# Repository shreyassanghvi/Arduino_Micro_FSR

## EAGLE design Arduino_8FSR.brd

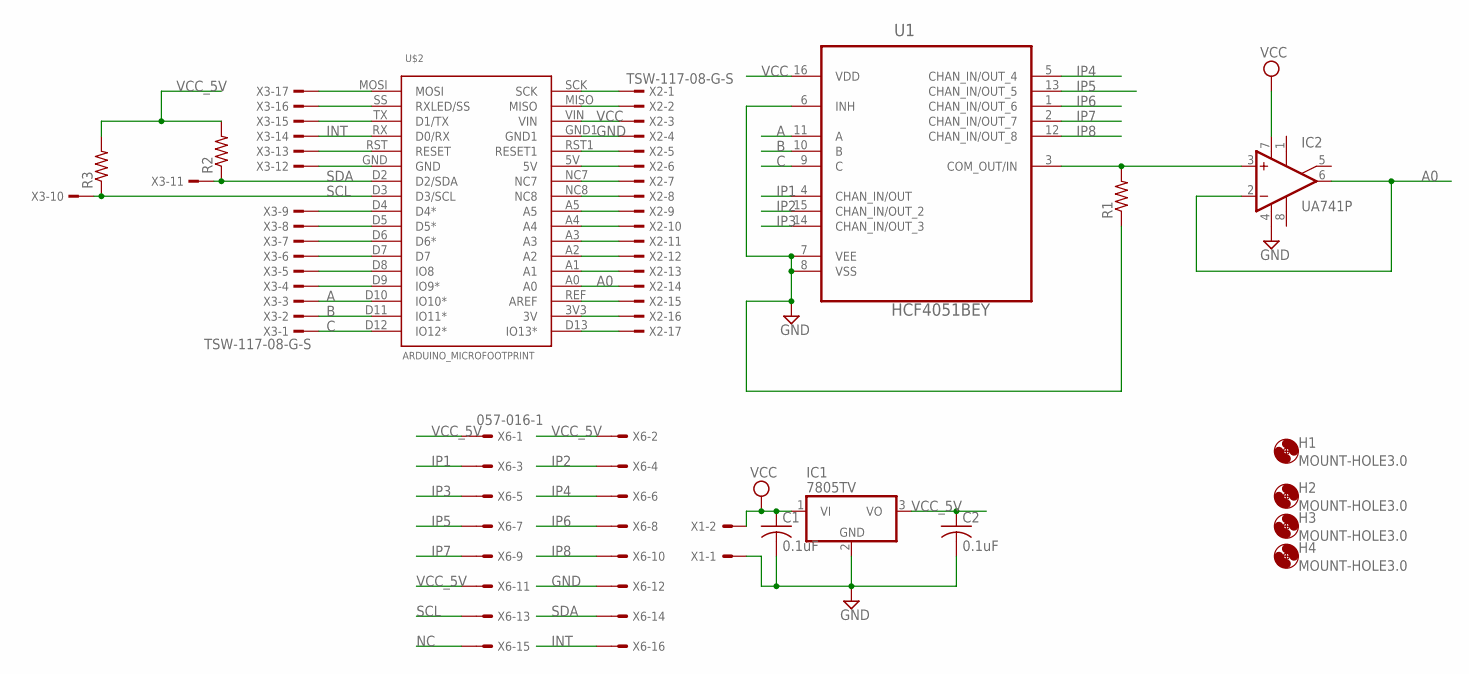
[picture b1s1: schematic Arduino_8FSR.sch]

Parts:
C1, C2: 0.1uF; C025-024X044
H1, H2, H3, H4: MOUNT-HOLE3.0; 3,0
IC1: 7805TV; TO220V
IC2: UA741P; DIL08
R1, R2, R3: R-US_0204/7; 0204/7
U1: HCF4051BEY; DIP254P762X510-16
U$2: ARDUINO_MICROFOOTPRINT; ARDUINO-MICRO
X1: KK-156-2
X2, X3: TSW-117-08-G-S; TSW-117-XX-G-S
X6: 057-016-1

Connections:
A: U1.11 (A), U$2.D10 (IO10*), X3.3
A0: IC2.2 (-IN), IC2.6 (OUT), U$2.A0, X2.14
B: U1.10 (B), U$2.D11 (IO11*), X3.2
C: U1.9 (C), U$2.D12 (IO12*), X3.1
GND: C1.2, C2.2, IC1.2 (GND), IC2.4 (V-), R1.1, U1.6 (INH), U1.7 (VEE), U1.8 (VSS), U$2.GND1, X1.1, X2.4, X6.12
INT: U$2.RX (D0/RX), X3.14, X6.16
IP1: U1.4 (CHAN_IN/OUT), X6.3
IP2: U1.15 (CHAN_IN/OUT_2), X6.4
IP3: U1.14 (CHAN_IN/OUT_3), X6.5
IP4: U1.5 (CHAN_IN/OUT_4), X6.6
IP5: U1.13 (CHAN_IN/OUT_5), X6.7
IP6: U1.1 (CHAN_IN/OUT_6), X6.8
IP7: U1.2 (CHAN_IN/OUT_7), X6.9
IP8: U1.12 (CHAN_IN/OUT_8), X6.10
unnamed: U$2.MOSI, X3.17
unnamed: U$2.SS (RXLED/SS), X3.16
unnamed: U$2.D13 (IO13*), X2.17
unnamed: U$2.D5 (D5*), X3.8
unnamed: U$2.RST (RESET), X3.13
unnamed: U$2.GND, X3.12
unnamed: U$2.D6 (D6*), X3.7
unnamed: U$2.D7, X3.6
unnamed: U$2.D4 (D4*), X3.9
unnamed: U$2.TX (D1/TX), X3.15
unnamed: U$2.D8 (IO8), X3.5
unnamed: U$2.D9 (IO9*), X3.4
unnamed: U$2.3V3 (3V), X2.16
unnamed: U$2.REF (AREF), X2.15
unnamed: U$2.A1, X2.13
unnamed: U$2.A2, X2.12
unnamed: U$2.A3, X2.11
unnamed: U$2.A4, X2.10
unnamed: U$2.A5, X2.9
unnamed: U$2.NC8, X2.8
unnamed: U$2.NC7, X2.7
unnamed: U$2.5V, X2.6
unnamed: U$2.RST1 (RESET1), X2.5
unnamed: U$2.MISO, X2.2
unnamed: U$2.SCK, X2.1
unnamed: IC2.3 (+IN), R1.2, U1.3 (COM_OUT/IN)
NC: X6.15
SCL: R3.1, U$2.D3 (D3/SCL), X3.10, X6.13
SDA: R2.1, U$2.D2 (D2/SDA), X3.11, X6.14
VCC: C1.1, IC1.1 (VI), IC2.7 (V+), U1.16 (VDD), U$2.VIN, X1.2, X2.3
VCC_5V: C2.1, IC1.3 (VO), R2.2, R3.2, X6.1, X6.2, X6.11

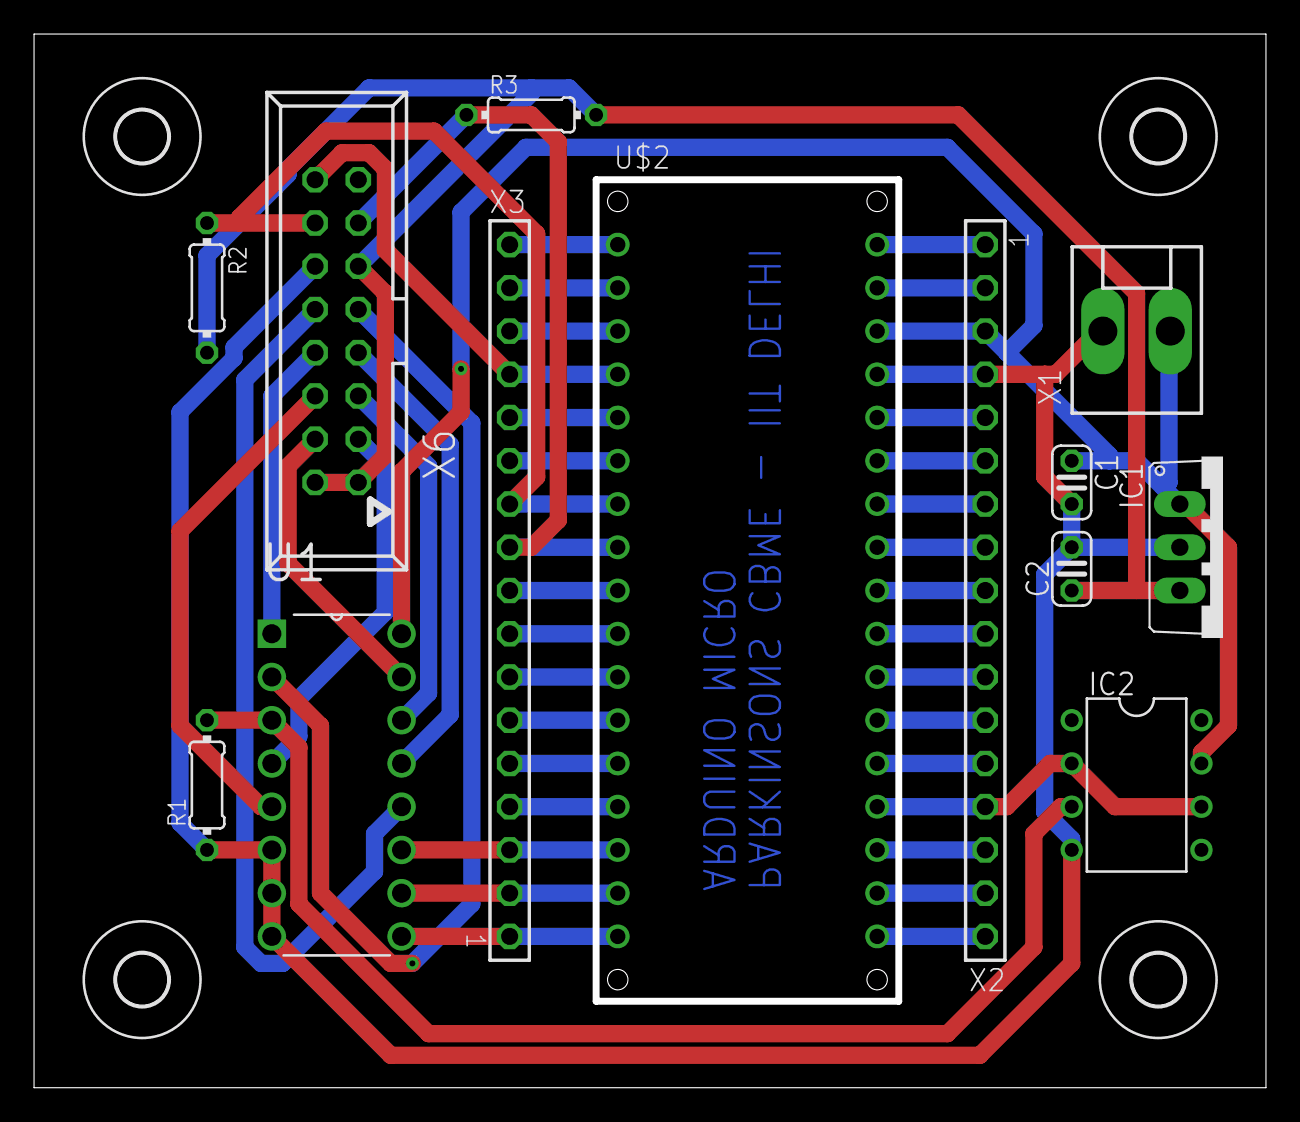
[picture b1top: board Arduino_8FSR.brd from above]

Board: 2 copper layers, 72.0 x 61.5 mm, 17 parts (0 on the bottom side), 44 nets.

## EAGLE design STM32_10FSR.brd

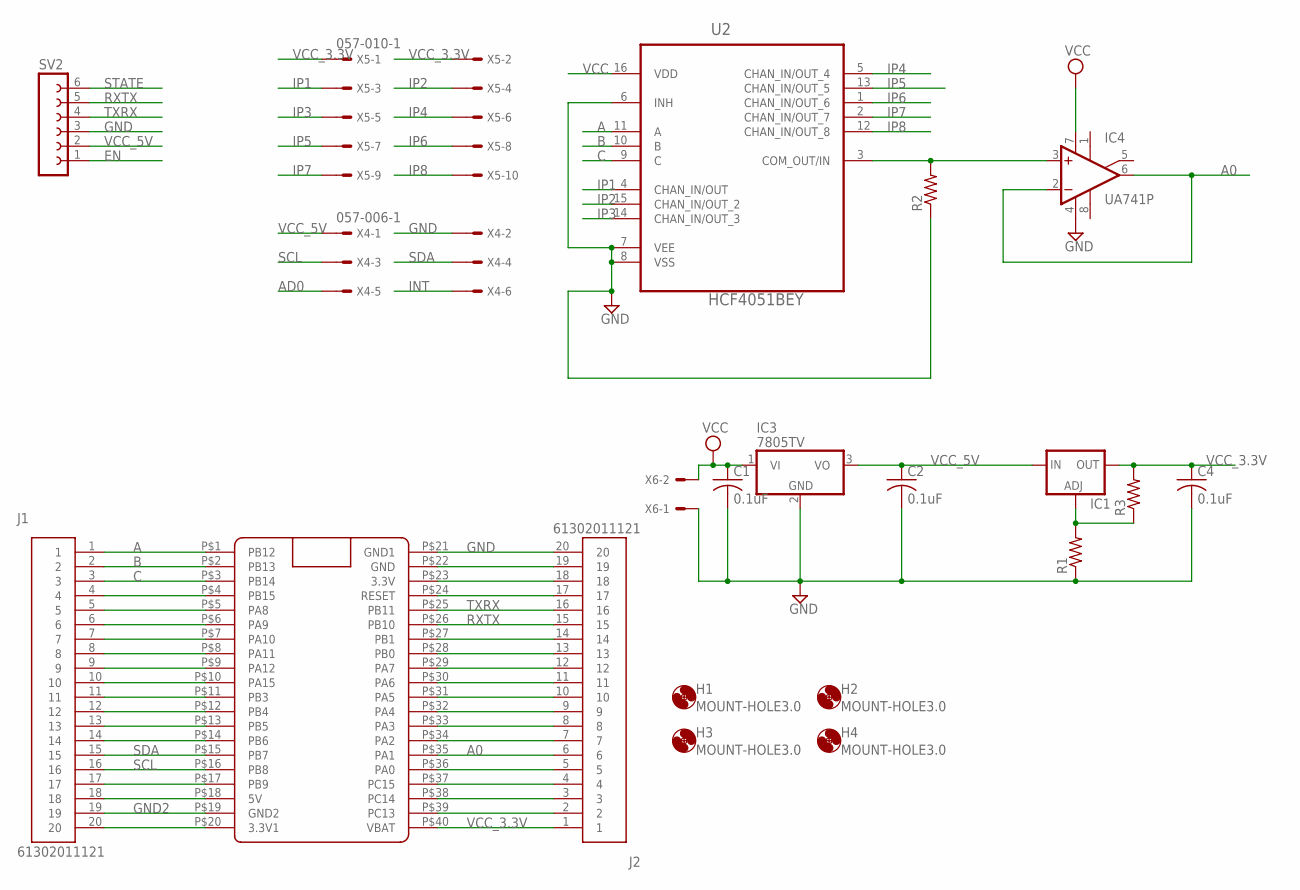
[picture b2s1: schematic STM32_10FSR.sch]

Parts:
C1, C2, C4: 0.1uF; C025-024X044
H1, H2, H3, H4: MOUNT-HOLE3.0; 3,0
IC1: LM317TS; 317TS
IC3: 7805TV; TO220V
IC4: UA741P; DIL08
J1, J2: 61302011121
R1, R2, R3: R-US_0204/7; 0204/7
SV2: FE06-1; FE06
U2: HCF4051BEY; DIP254P762X510-16
U$1: BLUE_PILLADVANCED; BLUE_PILL_ADV
X4: 057-006-1
X5: 057-010-1
X6: KK-156-2

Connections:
A: J1.1, U2.11 (A), U$1.P$1 (PB12)
A0: IC4.2 (-IN), IC4.6 (OUT), J2.6, U$1.P$35 (PA1)
AD0: X4.5
B: J1.2, U2.10 (B), U$1.P$2 (PB13)
C: J1.3, U2.9 (C), U$1.P$3 (PB14)
EN: SV2.1
GND: C1.2, C2.2, C4.2, IC3.2 (GND), IC4.4 (V-), J2.20, R1.1, R2.1, SV2.3, U2.6 (INH), U2.7 (VEE), U2.8 (VSS), U$1.P$21 (GND1), X4.2, X6.1
GND2: J1.19, U$1.P$19 (GND2)
INT: X4.6
IP1: U2.4 (CHAN_IN/OUT), X5.3
IP2: U2.15 (CHAN_IN/OUT_2), X5.4
IP3: U2.14 (CHAN_IN/OUT_3), X5.5
IP4: U2.5 (CHAN_IN/OUT_4), X5.6
IP5: U2.13 (CHAN_IN/OUT_5), X5.7
IP6: U2.1 (CHAN_IN/OUT_6), X5.8
IP7: U2.2 (CHAN_IN/OUT_7), X5.9
IP8: U2.12 (CHAN_IN/OUT_8), X5.10
unnamed: J1.6, U$1.P$6 (PA9)
unnamed: J1.7, U$1.P$7 (PA10)
unnamed: J2.5, U$1.P$36 (PA0)
unnamed: J1.4, U$1.P$4 (PB15)
unnamed: J1.5, U$1.P$5 (PA8)
unnamed: J1.8, U$1.P$8 (PA11)
unnamed: J1.9, U$1.P$9 (PA12)
unnamed: J1.10, U$1.P$10 (PA15)
unnamed: J1.11, U$1.P$11 (PB3)
unnamed: J1.12, U$1.P$12 (PB4)
unnamed: J1.13, U$1.P$13 (PB5)
unnamed: J1.14, U$1.P$14 (PB6)
unnamed: J1.17, U$1.P$17 (PB9)
unnamed: J1.18, U$1.P$18 (5V)
unnamed: J1.20, U$1.P$20 (3.3V1)
unnamed: IC1.1 (ADJ), R1.2, R3.1
unnamed: J2.2, U$1.P$39 (PC13)
unnamed: J2.3, U$1.P$38 (PC14)
unnamed: J2.4, U$1.P$37 (PC15)
unnamed: J2.7, U$1.P$34 (PA2)
unnamed: J2.8, U$1.P$33 (PA3)
unnamed: J2.9, U$1.P$32 (PA4)
unnamed: J2.10, U$1.P$31 (PA5)
unnamed: J2.11, U$1.P$30 (PA6)
unnamed: J2.12, U$1.P$29 (PA7)
unnamed: J2.13, U$1.P$28 (PB0)
unnamed: J2.14, U$1.P$27 (PB1)
unnamed: J2.17, U$1.P$24 (RESET)
unnamed: J2.18, U$1.P$23 (3.3V)
unnamed: J2.19, U$1.P$22 (GND)
unnamed: IC4.3 (+IN), R2.2, U2.3 (COM_OUT/IN)
RXTX: J2.15, SV2.5, U$1.P$26 (PB10)
SCL: J1.16, U$1.P$16 (PB8), X4.3
SDA: J1.15, U$1.P$15 (PB7), X4.4
STATE: SV2.6
TXRX: J2.16, SV2.4, U$1.P$25 (PB11)
VCC: C1.1, IC3.1 (VI), IC4.7 (V+), U2.16 (VDD), X6.2
VCC_3.3V: C4.1, IC1.2 (OUT), J2.1, R3.2, U$1.P$40 (VBAT), X5.1, X5.2
VCC_5V: C2.1, IC1.3 (IN), IC3.3 (VO), SV2.2, X4.1

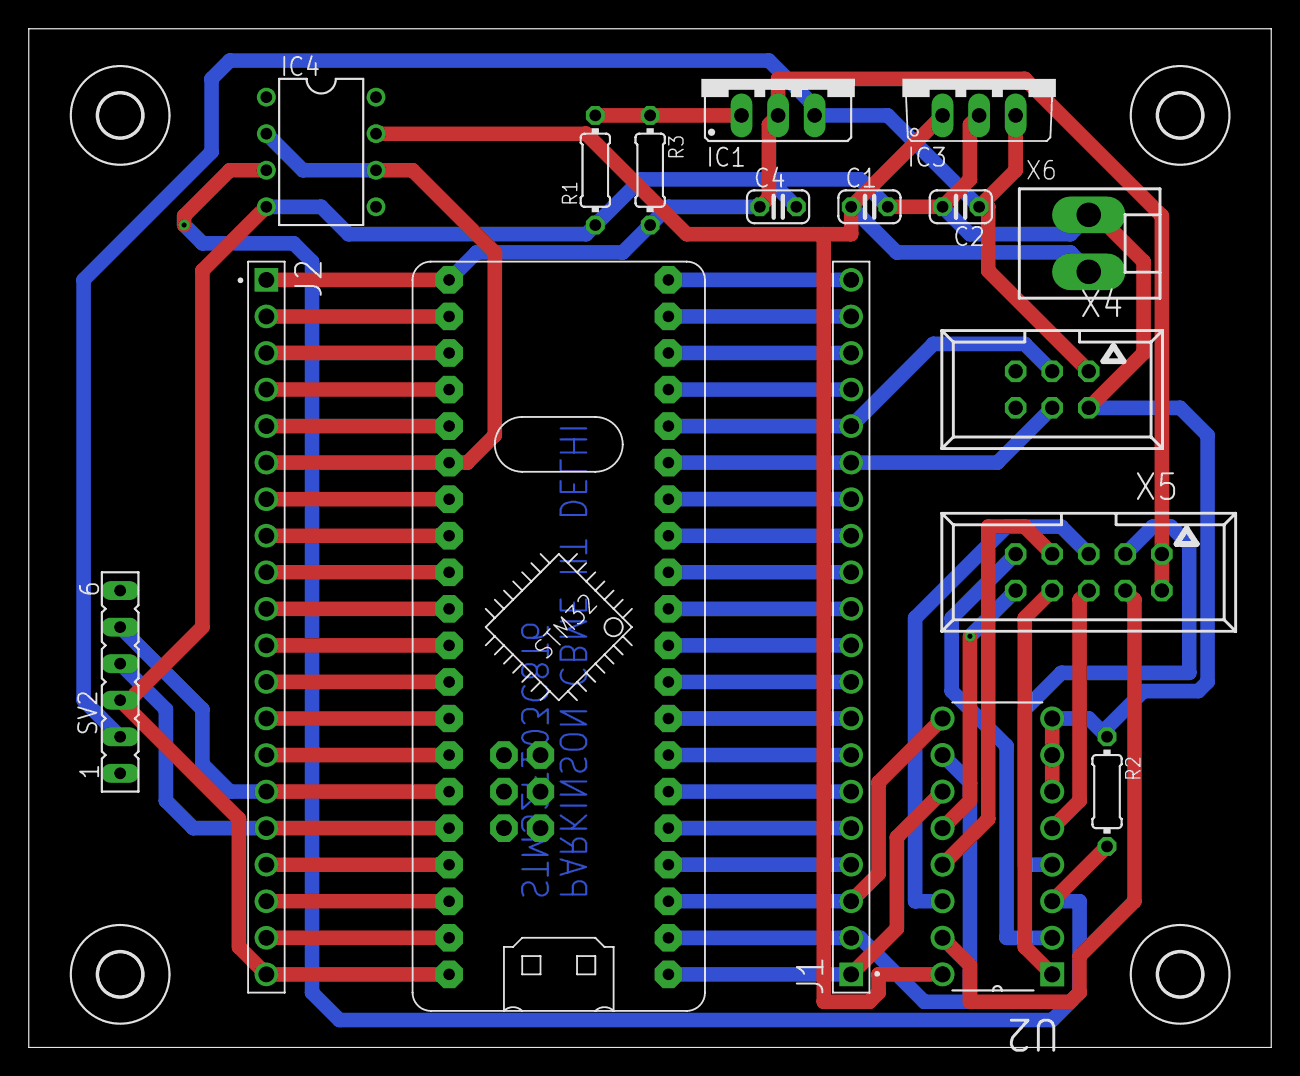
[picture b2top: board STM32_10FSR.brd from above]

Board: 2 copper layers, 86.3 x 70.8 mm, 21 parts (0 on the bottom side), 52 nets.

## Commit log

2020-03-04 04032020
2020-03-05 Final Version
2020-03-05 Final update V1
